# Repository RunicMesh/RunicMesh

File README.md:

# RunicMesh 🔮⚡

*A versatile, solar-powered Meshtastic node built on ESP32.*

## Overview

RunicMesh is a custom-built Meshtastic node designed for off-grid, long-range communication. It features:

- Hybrid power – USB-C + solar (prioritizing solar charging) ☀️🔋
- Deep sleep optimization for ultra-low power consumption ⚡
- Modular expandability – screen support via plug-in connector 📟
- Built on ESP32, designed for mobility and versatility 📡

## Will feature

- Meshtastic Compatibility – Seamlessly integrates with the Meshtastic ecosystem.
- Solar-Powered & Energy-Efficient – Smart power management for extended field use.
- Modular Design – Screen support, optional GPS, and future expandability.
- Off-Grid Ready – No internet required, all telemetry goes over the mesh network.

## Project Goals

📡 Enhance off-grid mesh networking

🔋 Maximize energy efficiency

🛠️ Offer modularity & expandability

## Hardware

- ESP32-based (exact model TBD)
- Battery: 1S1P or 1S2P 18650 (depending on final power needs)
- Hybrid charging: USB-C + solar priority
- Optional GPS for mobile tracking
- Plug-in screen support

## Software & Firmware

- Meshtastic firmware customization
- Deep sleep implementation for power efficiency
- Telemetry transmission over the mesh network

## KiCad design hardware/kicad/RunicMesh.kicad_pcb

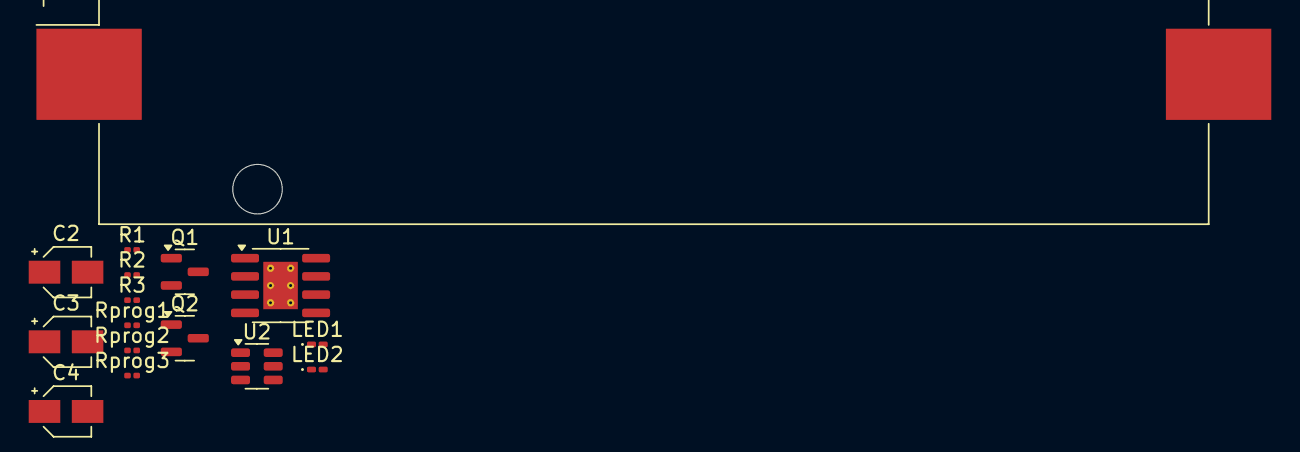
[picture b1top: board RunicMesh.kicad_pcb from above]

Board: 2 copper layers, 16 parts (0 on the bottom side), 15 nets, no tracks yet.

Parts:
Battery1: 18650; BatteryHolder_Keystone_1042_1x18650
C2, C3: 10µF; CP_Elec_3x5.3
C4: 0.1µF; CP_Elec_3x5.3
LED1: G; LED_0201_0603Metric_Pad0.64x0.40mm_HandSolder
LED2: R; LED_0201_0603Metric_Pad0.64x0.40mm_HandSolder
Q1, Q2: IRLML6244; SOT-23
R1, R2: 1k; R_0201_0603Metric
R3: 0.4; R_0201_0603Metric
Rprog1: 1.2K; R_0201_0603Metric
Rprog2: 1K; R_0201_0603Metric
Rprog3: 100; R_0201_0603Metric
U1: TP4056-42-ESOP8; SOIC-8-1EP_3.9x4.9mm_P1.27mm_EP2.41x3.3mm_ThermalVias
U2: DW01A; SOT-23-6

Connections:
+5V: R3.2, U1.4 (V_{CC})
B+: Battery1.1 (+), C3.1, Rprog3.2, U1.5 (BAT)
B-: Q2.2 (S), Rprog2.1
GND: Battery1.2 (-), C2.2, C3.2, C4.2, Q1.2 (S), Rprog1.1, U1.1 (TEMP), U1.3 (GND), U1.9 (EPAD), U2.6 (GND)
unnamed: LED1.2 (A), R2.1
unnamed: C2.1, LED1.1 (K), LED2.1 (K), R3.1, U1.8 (CE)
unnamed: LED2.2 (A), R1.1
unnamed: Q1.3 (D), Q2.3 (D)
unnamed: Q1.1 (G), U2.1 (OD)
unnamed: Q2.1 (G), U2.3 (OC)
unnamed: Rprog1.2, U1.2 (PROG)
unnamed: R1.2, U1.7 (~CHRG)
unnamed: R2.2, U1.6 (~STDBY)
unnamed: Rprog2.2, U2.2 (CS)
unnamed: C4.1, Rprog3.1, U2.5 (VCC)

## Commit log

2025-02-27 Add base README
2025-03-11 Power part done mostly
2025-03-11 Change power/charging circuit to have LED for chargin status
2025-03-11 Update power part with overdischarge and overcharge protections
2025-03-11 updates to the schematic
